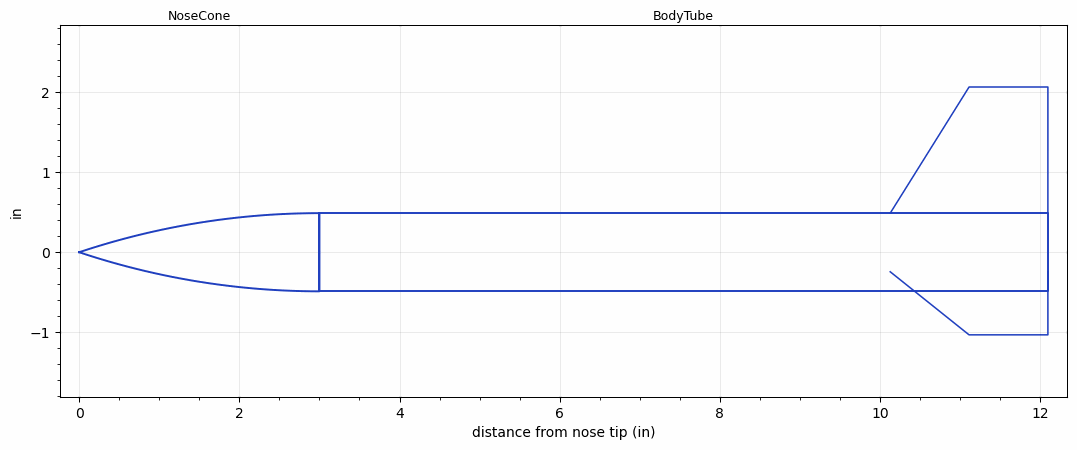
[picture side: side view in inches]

<RASAeroDocument>
 <FileVersion>2</FileVersion>
 <RocketDesign>
  <NoseCone>
   <Length>3</Length>
   <Diameter>0.976</Diameter>
   <Shape>Tangent Ogive</Shape>
   <Location>0</Location>
  </NoseCone>
  <BodyTube>
   <Length>9.0945</Length>
   <Diameter>0.976</Diameter>
   <Location>3</Location>
   <Fin>
    <Count>3</Count>
    <Chord>1.9685</Chord>
    <Span>1.5748</Span>
    <SweepDistance>0.9843</SweepDistance>
    <TipChord>0.9843</TipChord>
    <Thickness>0.0591</Thickness>
    <Location>1.9685</Location>
    <AirfoilSection>Rounded</AirfoilSection>
   </Fin>
  </BodyTube>
  <Surface>Rough Camouflage Paint</Surface>
  <ModifiedBarrowman>False</ModifiedBarrowman>
  <Turbulence>False</Turbulence>
  <UseBooster1>False</UseBooster1>
  <UseBooster2>False</UseBooster2>
 </RocketDesign>
 <LaunchSite>
  <Altitude>0</Altitude>
  <Pressure>0</Pressure>
  <RodAngle>0</RodAngle>
  <RodLength>3.28</RodLength>
  <Temperature>59</Temperature>
  <WindSpeed>0</WindSpeed>
 </LaunchSite>
 <Recovery>
  <Altitude1>1000</Altitude1>
  <Altitude2>1000</Altitude2>
  <DeviceType1>None</DeviceType1>
  <DeviceType2>None</DeviceType2>
  <Event1>False</Event1>
  <Event2>False</Event2>
  <Size1>1</Size1>
  <Size2>1</Size2>
  <EventType1>None</EventType1>
  <EventType2>None</EventType2>
  <CD1>1.33</CD1>
  <CD2>1.33</CD2>
 </Recovery>
 <SimulationList>
  <Simulation>
   <SustainerEngine>C6  (ES)</SustainerEngine>
   <SustainerLaunchWt>0.12</SustainerLaunchWt>
   <SustainerCG>7.87</SustainerCG>
   <SustainerIgnitionDelay>0</SustainerIgnitionDelay>
   <Booster1SeparationDelay>0</Booster1SeparationDelay>
   <Booster1IgnitionDelay>0</Booster1IgnitionDelay>
   <IncludeBooster1>False</IncludeBooster1>
   <Booster2Delay>0</Booster2Delay>
   <IncludeBooster2>False</IncludeBooster2>
   <TimetoApogee>8.560101</TimetoApogee>
   <MaxAltitude>1425.41</MaxAltitude>
   <MaxVelocity>415.6726</MaxVelocity>
  </Simulation>
  <Simulation>
   <SustainerEngine>C6  (ES)</SustainerEngine>
   <SustainerLaunchWt>0.13</SustainerLaunchWt>
   <SustainerCG>7.87</SustainerCG>
   <SustainerIgnitionDelay>0</SustainerIgnitionDelay>
   <Booster1SeparationDelay>0</Booster1SeparationDelay>
   <Booster1IgnitionDelay>0</Booster1IgnitionDelay>
   <IncludeBooster1>False</IncludeBooster1>
   <Booster2Delay>0</Booster2Delay>
   <IncludeBooster2>False</IncludeBooster2>
   <TimetoApogee>8.620102</TimetoApogee>
   <MaxAltitude>1382.368</MaxAltitude>
   <MaxVelocity>390.1864</MaxVelocity>
  </Simulation>
 </SimulationList>
</RASAeroDocument>
